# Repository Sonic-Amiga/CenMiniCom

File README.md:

# Schematics for the Centurion Minicomputer replica

This is my work in progress repository, documenting an attempt to build a replica of a
Centurion minicomputer. The repository is a fork of Meisaka's reverse engineering project
(https://github.com/Meisaka/CenMiniCom.git) and contains some modifications.

This is a rather complex project, consisting of a multiple boards. For more information about
boards, which have actually been worked on, please see a README.md file in corresponding board's
subdirectory.

#### IMPORTANT: Schematics are originally reverse engineered from multiple hi-res images of the various cards, so they may contain mistakes or errors.

# Contacts

Please direct all questions to pavel_fedin@mail.ru

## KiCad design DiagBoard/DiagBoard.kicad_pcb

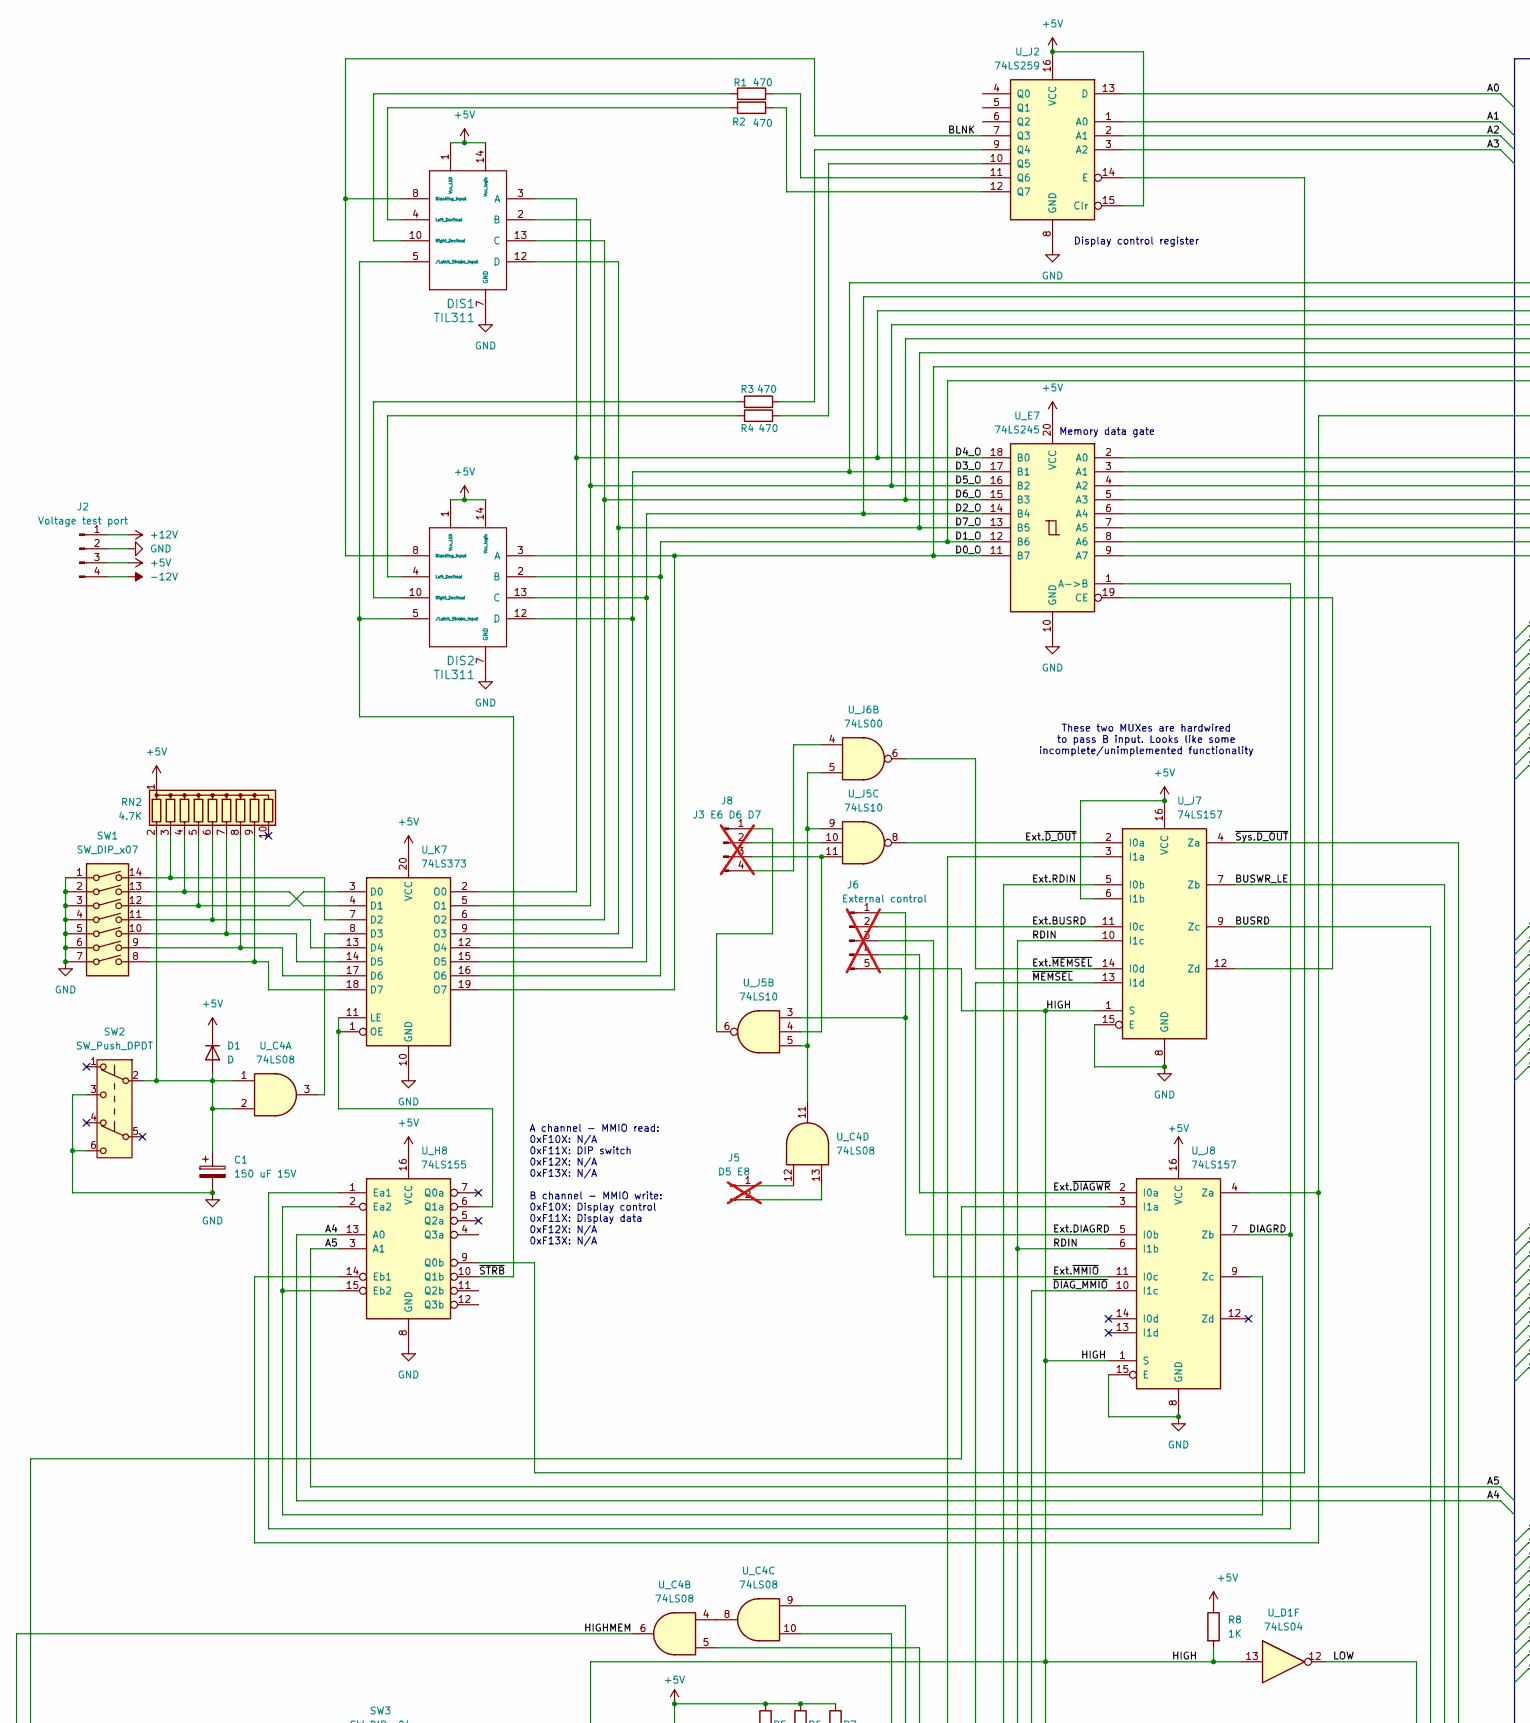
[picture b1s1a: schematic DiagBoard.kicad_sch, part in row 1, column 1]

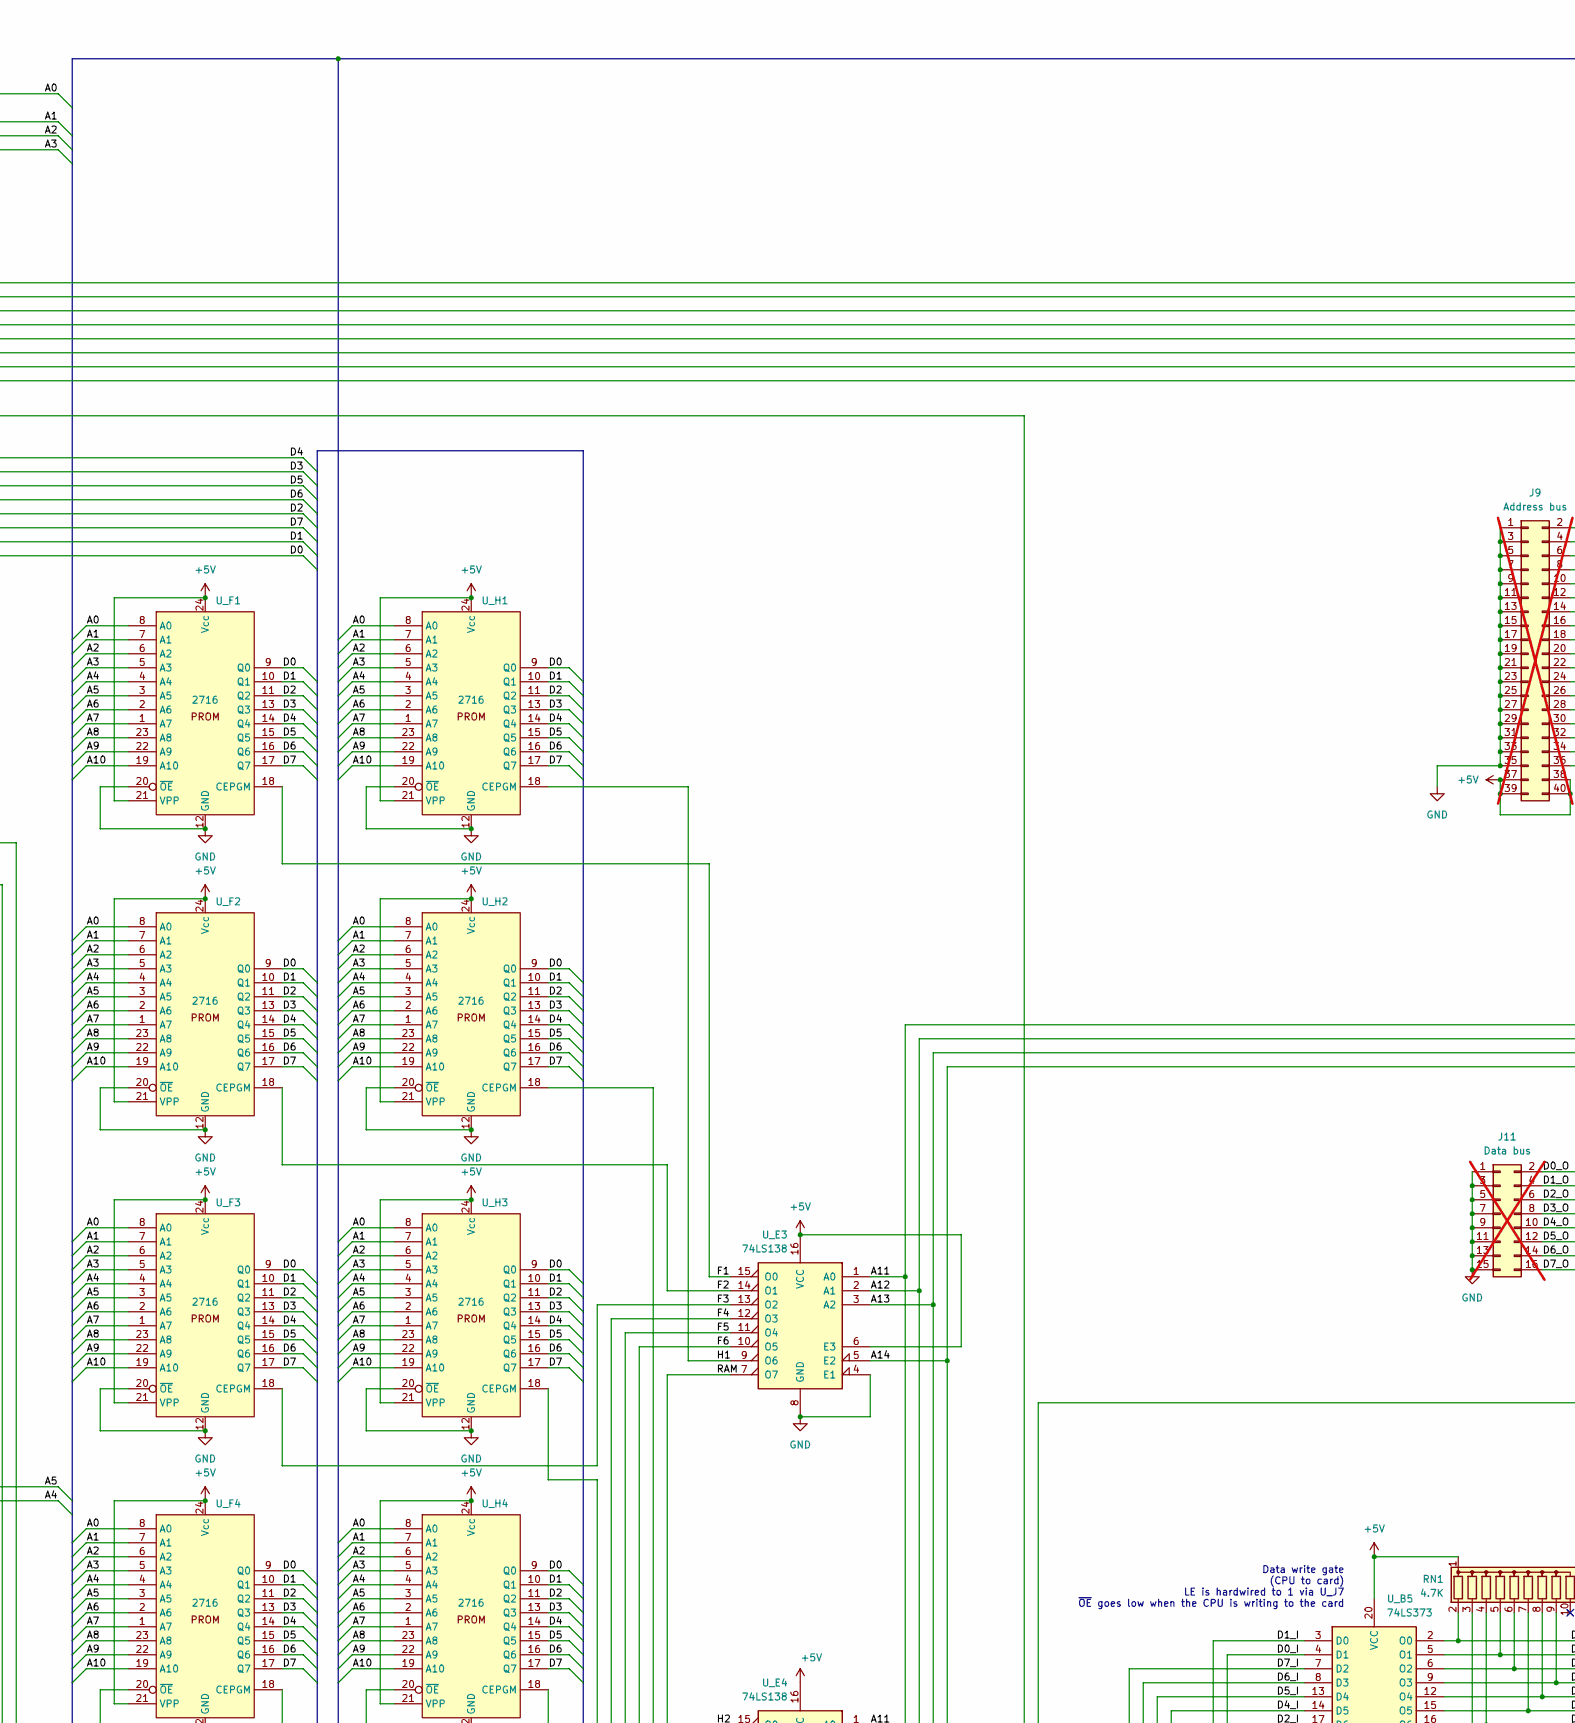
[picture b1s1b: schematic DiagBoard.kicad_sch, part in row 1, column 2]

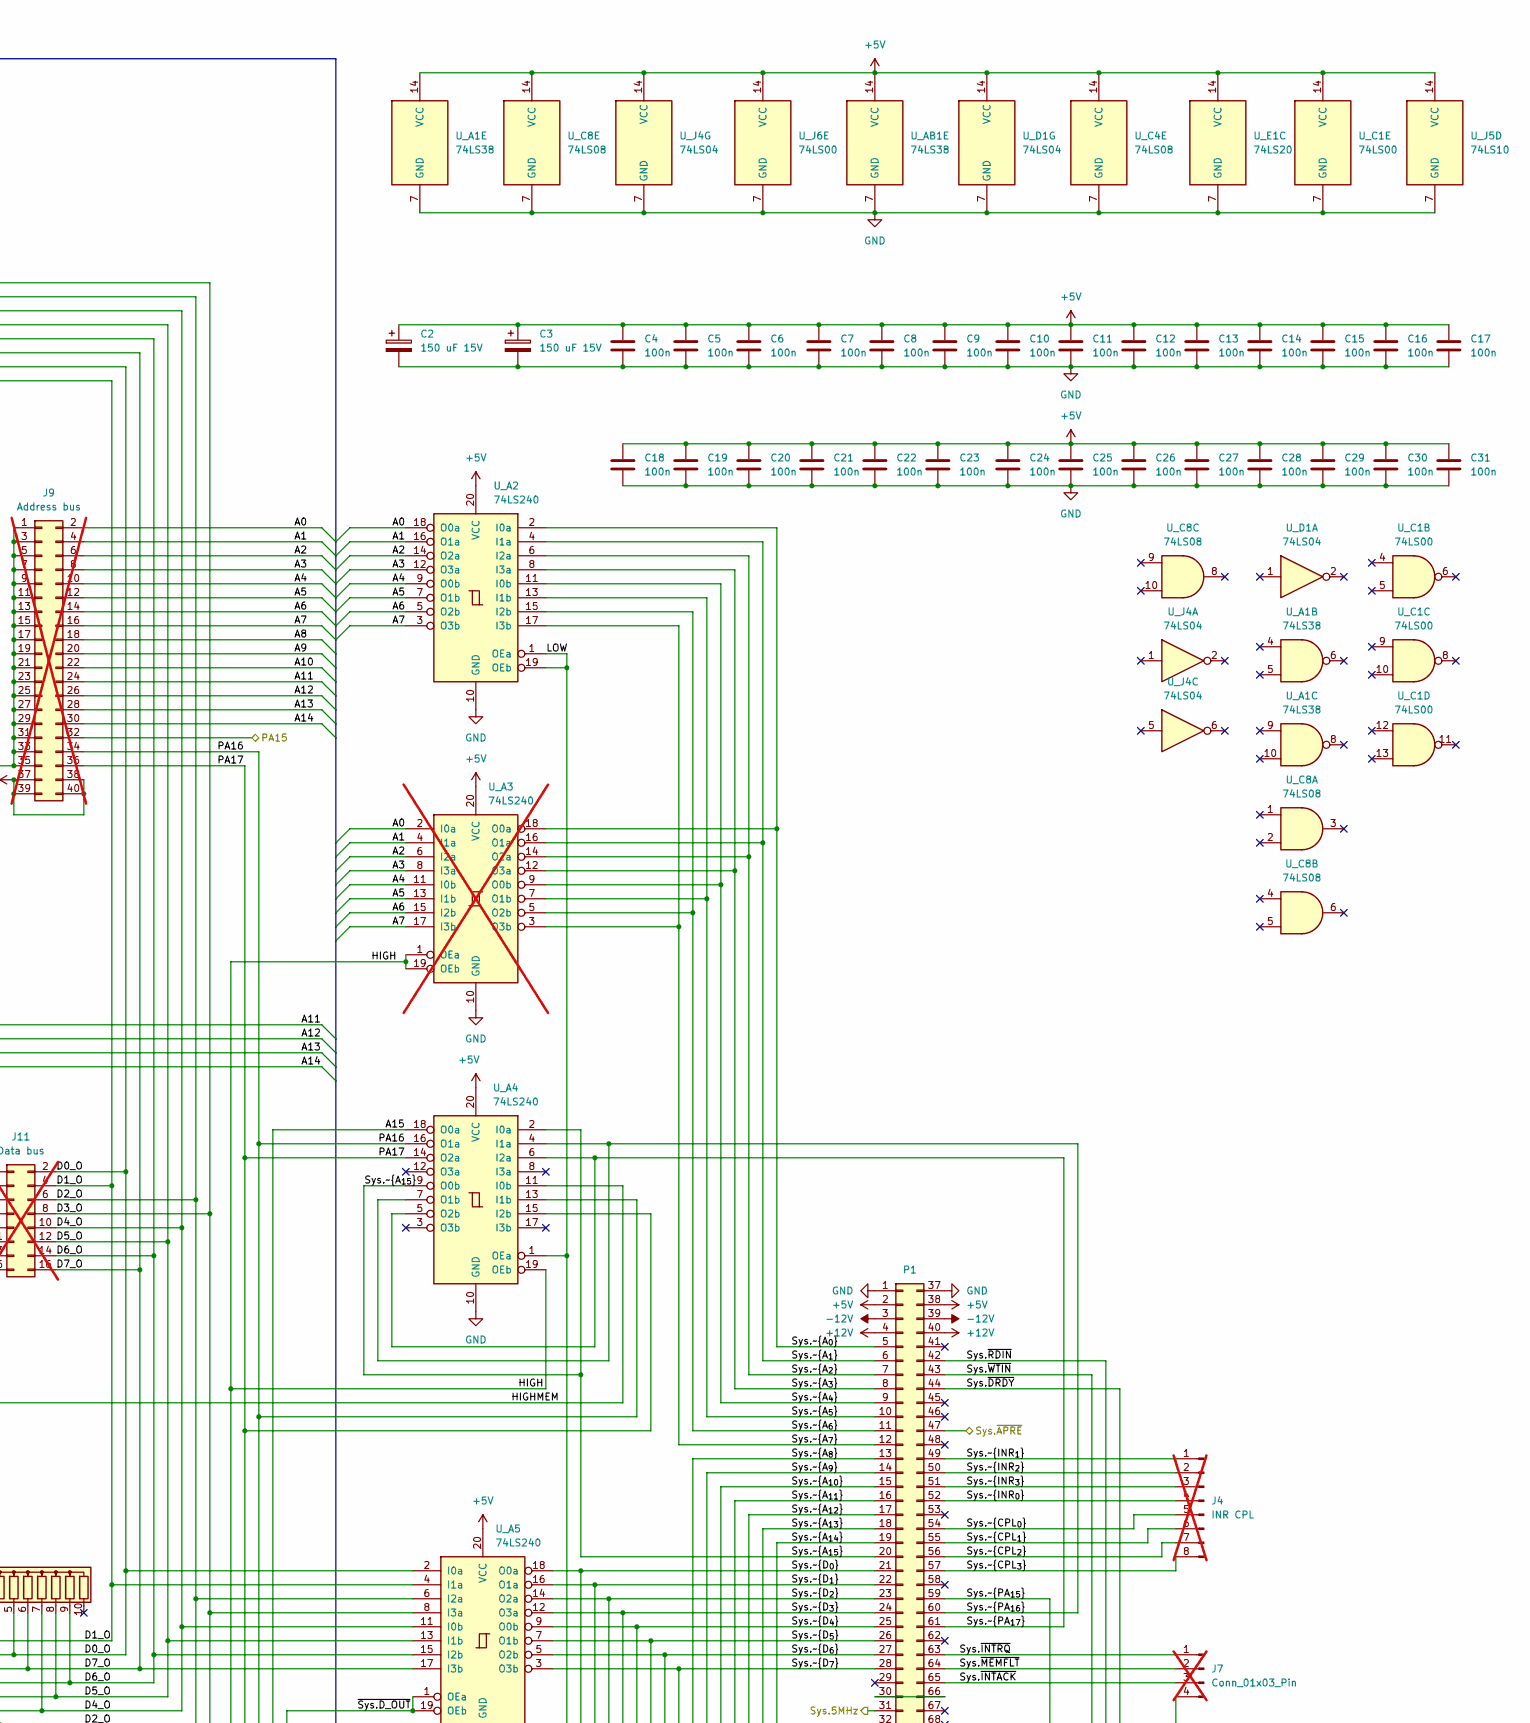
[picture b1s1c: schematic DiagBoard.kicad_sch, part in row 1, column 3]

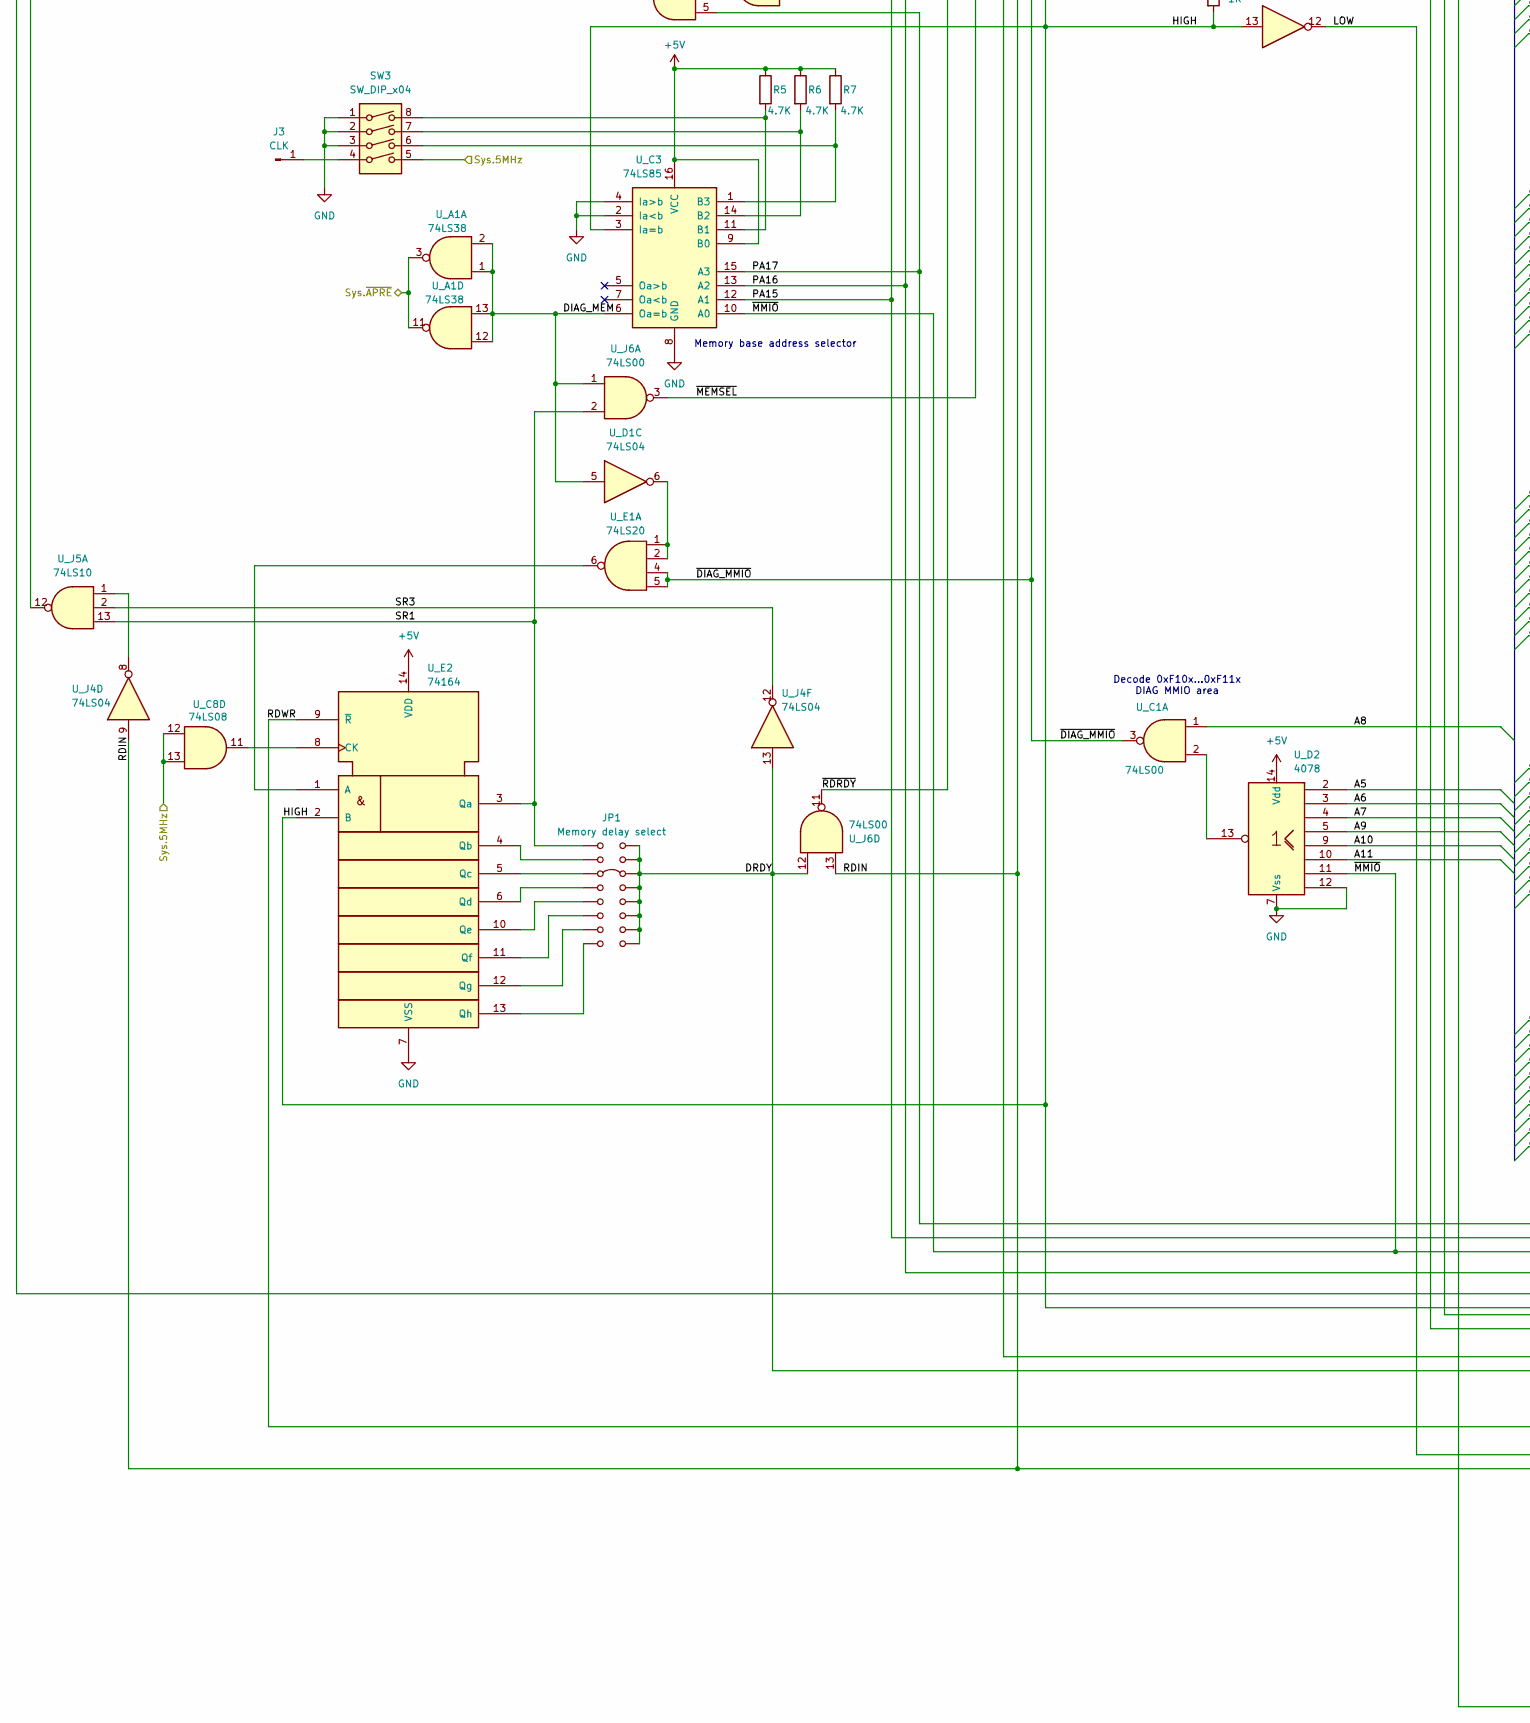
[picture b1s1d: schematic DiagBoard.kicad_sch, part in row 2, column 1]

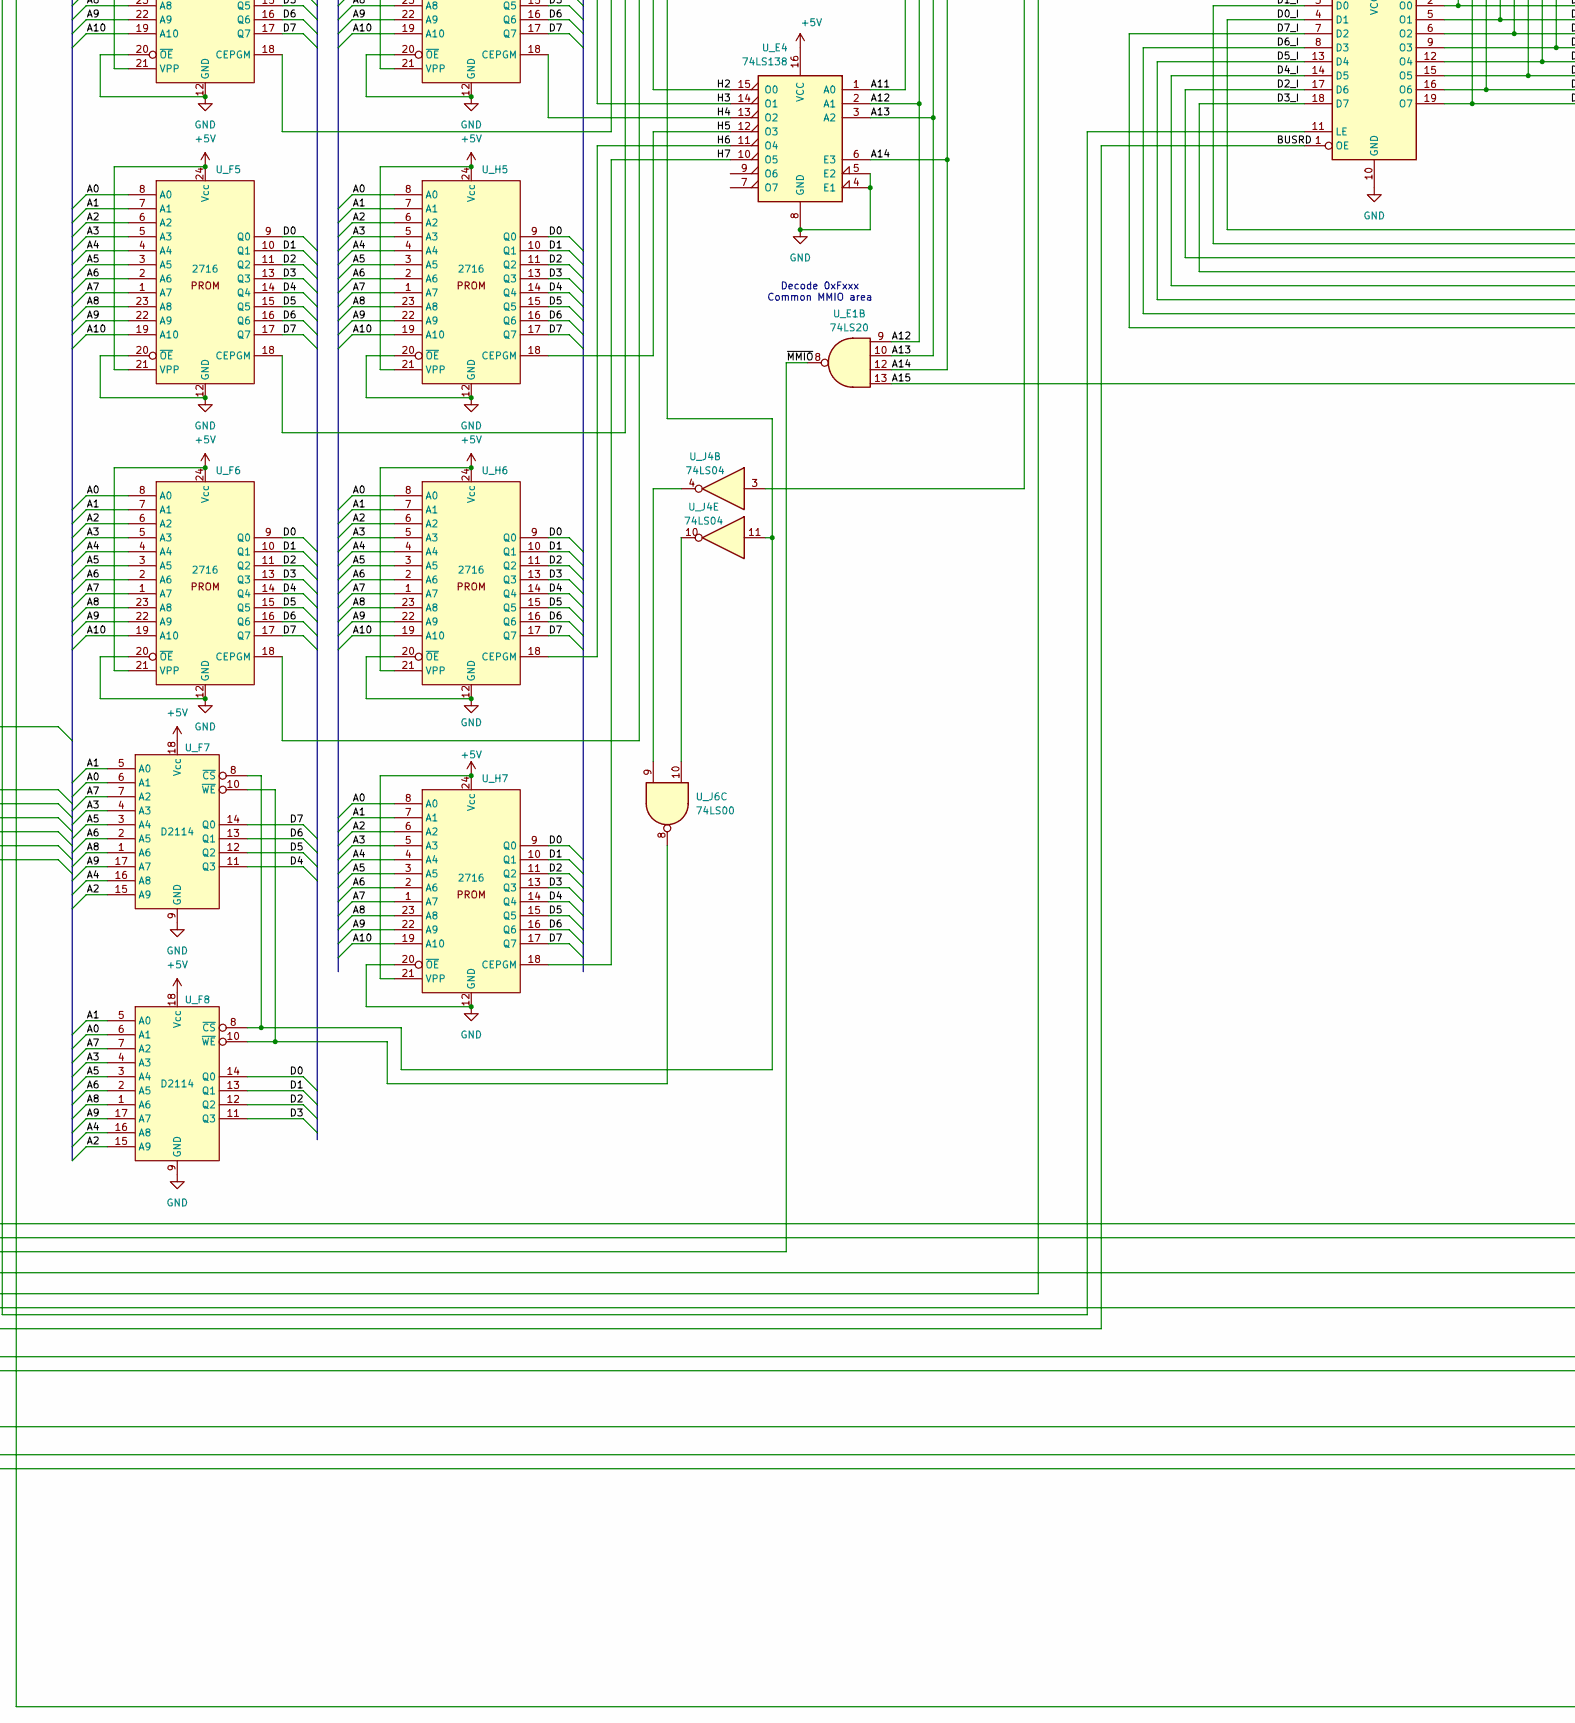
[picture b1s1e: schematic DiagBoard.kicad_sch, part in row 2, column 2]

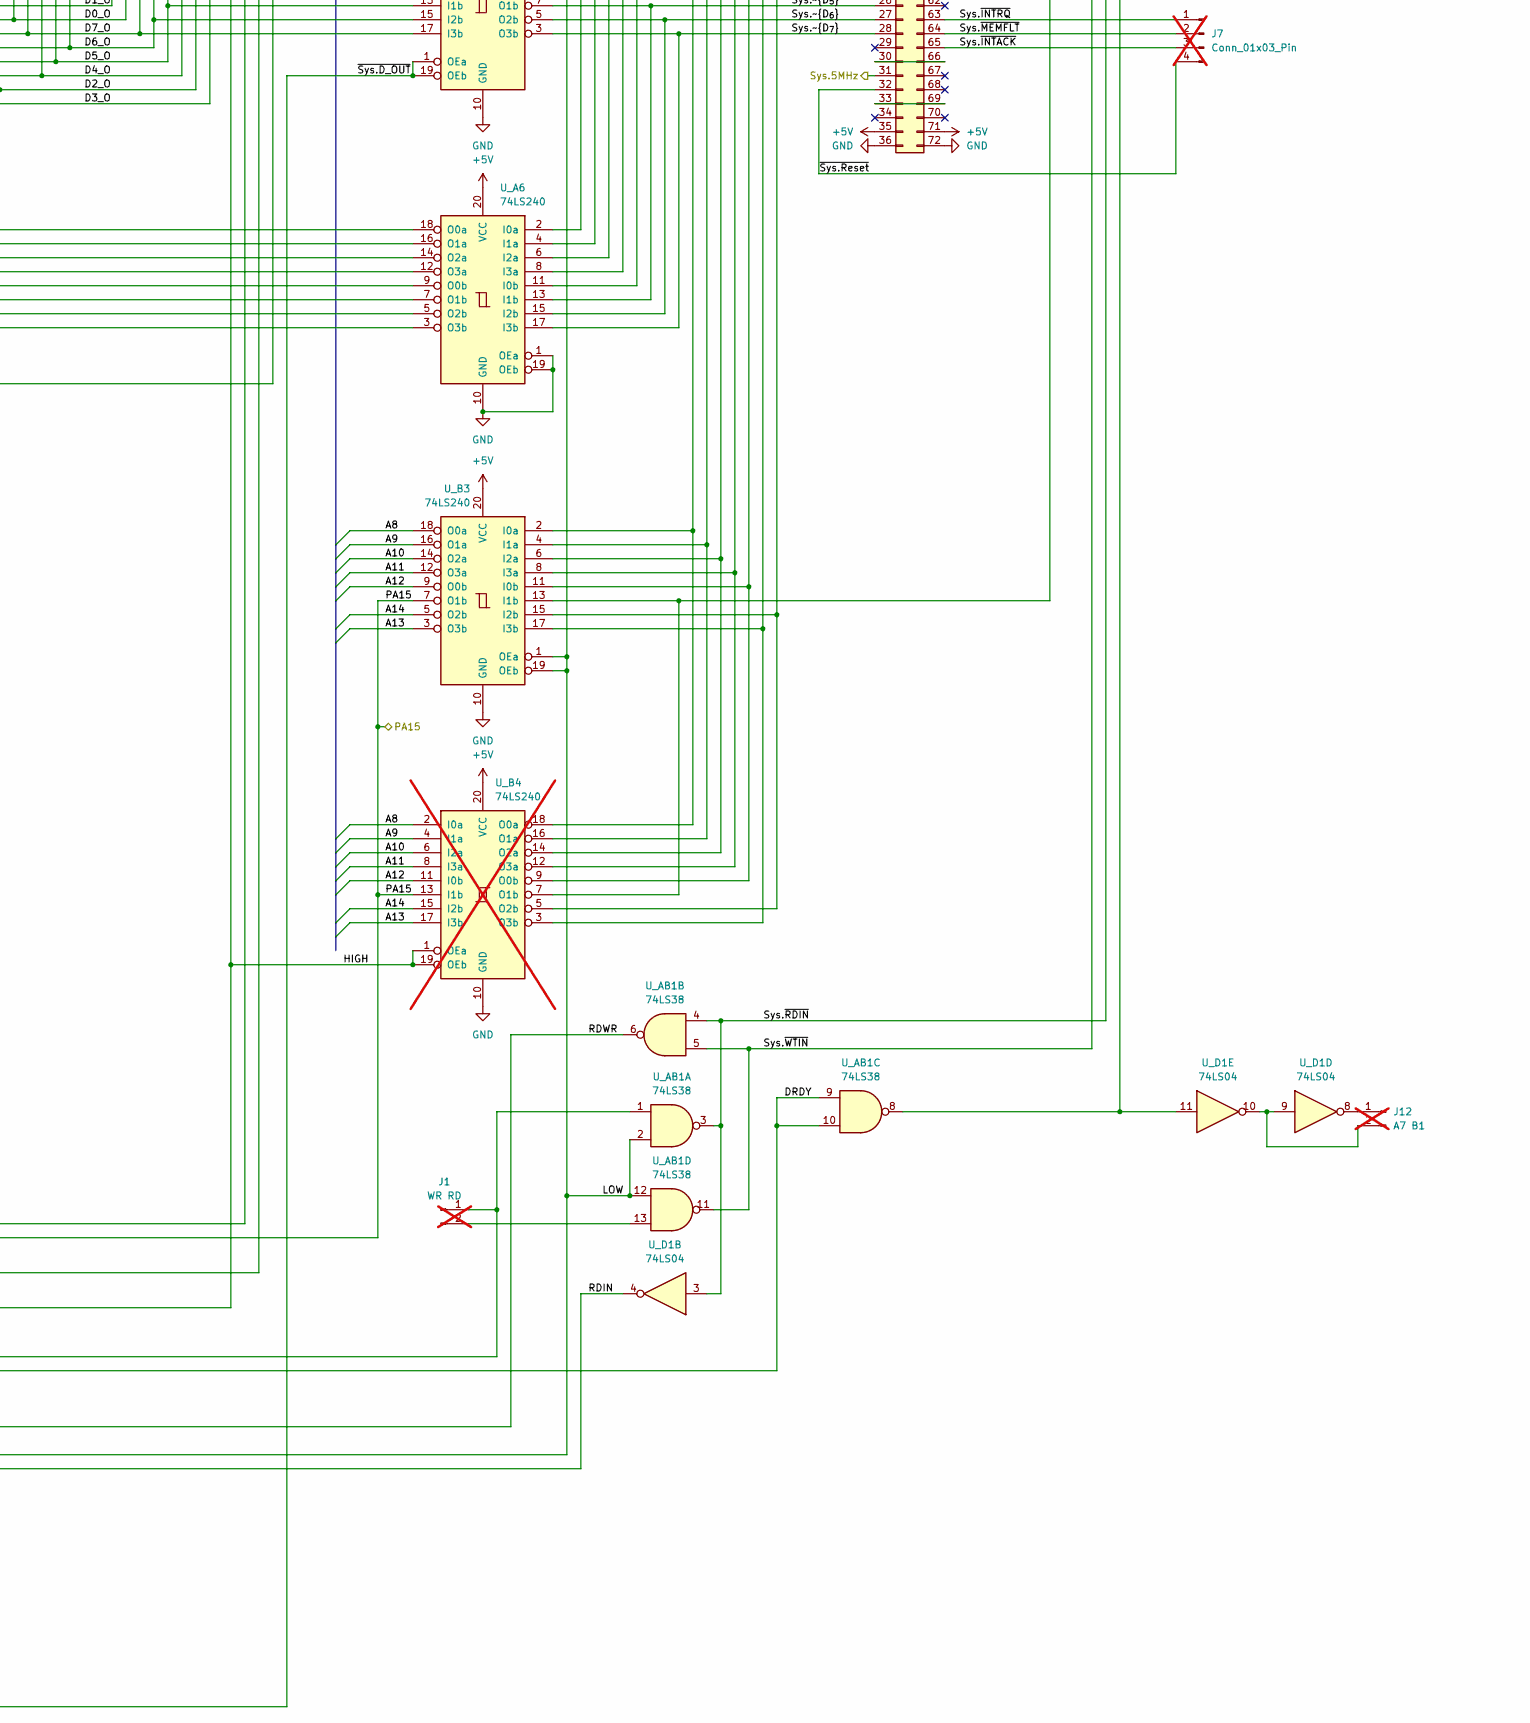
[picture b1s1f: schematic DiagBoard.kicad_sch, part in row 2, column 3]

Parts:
C1: 150 uF 15V; CP_Axial_L10.0mm_D4.5mm_P15.00mm_Horizontal
C2, C3: 150 uF 15V; CP_Axial_L25.0mm_D10.0mm_P30.00mm_Horizontal
C4, C5, C6, C7, C8, C9, C10, C11, C12, C13, C14, C15, C16, C17, C18, C19, C20, C21, C22, C23, C24, C25, C26, C27, C29, C30, C31: 100n; C_Disc_D4.3mm_W1.9mm_P5.00mm
C28: 100n; C_Rect_L9.0mm_W2.5mm_P7.50mm_MKT
D1: D; D_5W_P10.16mm_Horizontal
DIS1, DIS2: TIL311; DIP-14_W7.62mm_Socket
J1: WR RD; PinHeader_1x02_P2.54mm_Vertical; not fitted
J2: Voltage test port; Wago_734-134_1x04_P3.50mm_Vertical
J3: CLK; PinHeader_1x01_P2.54mm_Vertical
J4: INR CPL; PinHeader_1x08_P2.54mm_Vertical; not fitted
J5: D5 E8; PinHeader_1x02_P2.54mm_Vertical; not fitted
J6: External control; PinSocket_1x05_P2.54mm_Vertical; not fitted
J7: Conn_01x03_Pin; PinHeader_1x04_P2.54mm_Vertical; not fitted
J8: J3 E6 D6 D7; PinHeader_1x04_P2.54mm_Vertical; not fitted
J9: Address bus; IDC-Header_2x20_P2.54mm_Vertical; not fitted
J11: Data bus; IDC-Header_2x08_P2.54mm_Vertical; not fitted
J12: A7 B1; PinHeader_1x02_P2.54mm_Vertical; not fitted
JP1: Memory delay select; PinHeader_2x08_P2.54mm_Vertical
P1: Conn_02x36_Top_Bottom; BUS_EE200
R1, R2, R3, R4: 470; R_Axial_DIN0204_L3.6mm_D1.6mm_P7.62mm_Horizontal
R5, R6, R7: 4.7K; R_Axial_DIN0207_L6.3mm_D2.5mm_P10.16mm_Horizontal
R8: 1K; R_Axial_DIN0207_L6.3mm_D2.5mm_P10.16mm_Horizontal
RN1, RN2: 4.7K; R_Array_SIP10
SW1: SW_DIP_x07; SW_DIP_SPSTx07_Piano_10.8x19.34mm_W7.62mm_P2.54mm
SW2: SW_Push_DPDT; SW_Push_2P2T_Toggle_CK_PVA2OAH5xxxxxxV2
SW3: SW_DIP_x04; SW_DIP_SPSTx04_Slide_9.78x12.34mm_W7.62mm_P2.54mm
U_A1: 74LS38; DIP-14_W7.62mm
U_A2, U_A4, U_A5, U_A6: 74LS240; DIP-20_W7.62mm
U_A3: 74LS240; DIP-20_W7.62mm; not fitted
U_AB1: 74LS38; DIP-14_W7.62mm
U_B3: 74LS240; DIP-20_W7.62mm
U_B4: 74LS240; DIP-20_W7.62mm; not fitted
U_B5: 74LS373; DIP-20_W7.62mm
U_C1: 74LS00; DIP-14_W7.62mm
U_C3: 74LS85; DIP-16_W7.62mm
U_C4, U_C8: 74LS08; DIP-14_W7.62mm
U_D1: 74LS04; DIP-14_W7.62mm
U_D2: 4078; DIP-14_W7.62mm
U_E1: 74LS20; DIP-14_W7.62mm
U_E2: 74164; DIP-14_W7.62mm
U_E3, U_E4: 74LS138; DIP-16_W7.62mm
U_E7: 74LS245; DIP-20_W7.62mm
U_F1, U_F2, U_F3, U_F4, U_F5, U_F6: 2716; DIP-24_W15.24mm_Socket
U_F7, U_F8: D2114; DIP-18_W10.16mm
U_H1, U_H2, U_H3, U_H4, U_H5, U_H6, U_H7: 2716; DIP-24_W15.24mm_Socket
U_H8: 74LS155; DIP-16_W7.62mm
U_J2: 74LS259; DIP-16_W7.62mm
U_J4: 74LS04; DIP-14_W7.62mm
U_J5: 74LS10
U_J6: 74LS00; DIP-14_W7.62mm
U_J7, U_J8: 74LS157; DIP-16_W7.62mm
U_K7: 74LS373; DIP-20_W7.62mm

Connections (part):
+5V: C2.1, C3.1, C4.1, C5.1, C6.1, C7.1, C8.1, C9.1, C10.1, C11.1, C12.1, C13.1, C14.1, C15.1, C16.1, C17.1, C18.1, C19.1, C20.1, C21.1, C22.1, C23.1, C24.1, C25.1, C26.1, C27.1, C28.1, C29.1, C30.1, C31.1, D1.1 (K), DIS1.1 (Vcc_LED), DIS1.14 (Vcc_logic), DIS2.1 (Vcc_LED), DIS2.14 (Vcc_logic), J2.3, J9.37, J9.38, J9.39, J9.40, P1.2, P1.35, P1.38, P1.71, R5.1, R6.1, R7.1, R8.1, RN1.1 (common), RN2.1 (common), U_A1.14 (VCC), U_A2.20 (VCC), U_A3.20 (VCC), U_A4.20 (VCC), U_A5.20 (VCC), U_A6.20 (VCC), U_AB1.14 (VCC), U_B3.20 (VCC), U_B4.20 (VCC), U_B5.20 (VCC), U_C1.14 (VCC), U_C3.9 (B0), U_C3.16 (VCC), U_C4.14 (VCC), U_C8.14 (VCC), U_D1.14 (VCC), U_D2.14 (Vdd), U_E1.14 (VCC), U_E2.14 (VDD), U_E3.6 (E3), U_E3.16 (VCC), U_E4.16 (VCC), U_E7.20 (VCC), U_F1.21 (VPP), U_F1.24 (Vcc), U_F2.21 (VPP), U_F2.24 (Vcc), U_F3.21 (VPP), U_F3.24 (Vcc), U_F4.21 (VPP), U_F4.24 (Vcc), U_F5.21 (VPP), U_F5.24 (Vcc), U_F6.21 (VPP), U_F6.24 (Vcc)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
+12V: J2.1, P1.4, P1.40
-12V: J2.4, P1.3, P1.39
/A0: J9.2, U_A2.18 (O0a), U_A3.2 (I0a), U_F1.8 (A0), U_F2.8 (A0), U_F3.8 (A0), U_F4.8 (A0), U_F5.8 (A0), U_F6.8 (A0), U_F7.6 (A1), U_F8.6 (A1), U_H1.8 (A0), U_H2.8 (A0), U_H3.8 (A0), U_H4.8 (A0), U_H5.8 (A0), U_H6.8 (A0), U_H7.8 (A0), U_J2.13 (D)
/A1: J9.4, U_A2.16 (O1a), U_A3.4 (I1a), U_F1.7 (A1), U_F2.7 (A1), U_F3.7 (A1), U_F4.7 (A1), U_F5.7 (A1), U_F6.7 (A1), U_F7.5 (A0), U_F8.5 (A0), U_H1.7 (A1), U_H2.7 (A1), U_H3.7 (A1), U_H4.7 (A1), U_H5.7 (A1), U_H6.7 (A1), U_H7.7 (A1), U_J2.1 (A0)
/A2: J9.6, U_A2.14 (O2a), U_A3.6 (I2a), U_F1.6 (A2), U_F2.6 (A2), U_F3.6 (A2), U_F4.6 (A2), U_F5.6 (A2), U_F6.6 (A2), U_F7.15 (A9), U_F8.15 (A9), U_H1.6 (A2), U_H2.6 (A2), U_H3.6 (A2), U_H4.6 (A2), U_H5.6 (A2), U_H6.6 (A2), U_H7.6 (A2), U_J2.2 (A1)
/A3: J9.8, U_A2.12 (O3a), U_A3.8 (I3a), U_F1.5 (A3), U_F2.5 (A3), U_F3.5 (A3), U_F4.5 (A3), U_F5.5 (A3), U_F6.5 (A3), U_F7.4 (A3), U_F8.4 (A3), U_H1.5 (A3), U_H2.5 (A3), U_H3.5 (A3), U_H4.5 (A3), U_H5.5 (A3), U_H6.5 (A3), U_H7.5 (A3), U_J2.3 (A2)
/A4: J9.10, U_A2.9 (O0b), U_A3.11 (I0b), U_F1.4 (A4), U_F2.4 (A4), U_F3.4 (A4), U_F4.4 (A4), U_F5.4 (A4), U_F6.4 (A4), U_F7.16 (A8), U_F8.16 (A8), U_H1.4 (A4), U_H2.4 (A4), U_H3.4 (A4), U_H4.4 (A4), U_H5.4 (A4), U_H6.4 (A4), U_H7.4 (A4), U_H8.13 (A0)
/A5: J9.12, U_A2.7 (O1b), U_A3.13 (I1b), U_D2.2, U_F1.3 (A5), U_F2.3 (A5), U_F3.3 (A5), U_F4.3 (A5), U_F5.3 (A5), U_F6.3 (A5), U_F7.3 (A4), U_F8.3 (A4), U_H1.3 (A5), U_H2.3 (A5), U_H3.3 (A5), U_H4.3 (A5), U_H5.3 (A5), U_H6.3 (A5), U_H7.3 (A5), U_H8.3 (A1)
/A6: J9.14, U_A2.5 (O2b), U_A3.15 (I2b), U_D2.3, U_F1.2 (A6), U_F2.2 (A6), U_F3.2 (A6), U_F4.2 (A6), U_F5.2 (A6), U_F6.2 (A6), U_F7.2 (A5), U_F8.2 (A5), U_H1.2 (A6), U_H2.2 (A6), U_H3.2 (A6), U_H4.2 (A6), U_H5.2 (A6), U_H6.2 (A6), U_H7.2 (A6)
/A7: J9.16, U_A2.3 (O3b), U_A3.17 (I3b), U_D2.4, U_F1.1 (A7), U_F2.1 (A7), U_F3.1 (A7), U_F4.1 (A7), U_F5.1 (A7), U_F6.1 (A7), U_F7.7 (A2), U_F8.7 (A2), U_H1.1 (A7), U_H2.1 (A7), U_H3.1 (A7), U_H4.1 (A7), U_H5.1 (A7), U_H6.1 (A7), U_H7.1 (A7)
/A8: J9.18, U_B3.18 (O0a), U_B4.2 (I0a), U_C1.1, U_F1.23 (A8), U_F2.23 (A8), U_F3.23 (A8), U_F4.23 (A8), U_F5.23 (A8), U_F6.23 (A8), U_F7.1 (A6), U_F8.1 (A6), U_H1.23 (A8), U_H2.23 (A8), U_H3.23 (A8), U_H4.23 (A8), U_H5.23 (A8), U_H6.23 (A8), U_H7.23 (A8)
/A9: J9.20, U_B3.16 (O1a), U_B4.4 (I1a), U_D2.5, U_F1.22 (A9), U_F2.22 (A9), U_F3.22 (A9), U_F4.22 (A9), U_F5.22 (A9), U_F6.22 (A9), U_F7.17 (A7), U_F8.17 (A7), U_H1.22 (A9), U_H2.22 (A9), U_H3.22 (A9), U_H4.22 (A9), U_H5.22 (A9), U_H6.22 (A9), U_H7.22 (A9)
/A10: J9.22, U_B3.14 (O2a), U_B4.6 (I2a), U_D2.9, U_F1.19 (A10), U_F2.19 (A10), U_F3.19 (A10), U_F4.19 (A10), U_F5.19 (A10), U_F6.19 (A10), U_H1.19 (A10), U_H2.19 (A10), U_H3.19 (A10), U_H4.19 (A10), U_H5.19 (A10), U_H6.19 (A10), U_H7.19 (A10)
/A11: J9.24, U_B3.12 (O3a), U_B4.8 (I3a), U_D2.10, U_E3.1 (A0), U_E4.1 (A0)
/A12: J9.26, U_B3.9 (O0b), U_B4.11 (I0b), U_E1.9, U_E3.2 (A1), U_E4.2 (A1)
/A13: J9.28, U_B3.3 (O3b), U_B4.17 (I3b), U_E1.10, U_E3.3 (A2), U_E4.3 (A2)
/A14: J9.30, U_B3.5 (O2b), U_B4.15 (I2b), U_E1.12, U_E3.5 (E2), U_E4.6 (E3)
/A15: U_A4.18 (O0a), U_E1.13
/BLNK: DIS1.8 (Blanking_Input), DIS2.8 (Blanking_Input), U_J2.7 (Q3)
/BUSRD: U_B5.1 (OE), U_J7.9 (Zc)
/BUSWR_LE: U_B5.11 (LE), U_J7.7 (Zb)
/D0: U_E7.9 (A7), U_F1.9 (Q0), U_F2.9 (Q0), U_F3.9 (Q0), U_F4.9 (Q0), U_F5.9 (Q0), U_F6.9 (Q0), U_F8.14 (Q0), U_H1.9 (Q0), U_H2.9 (Q0), U_H3.9 (Q0), U_H4.9 (Q0), U_H5.9 (Q0), U_H6.9 (Q0), U_H7.9 (Q0)
/D0_I: U_A6.18 (O0a), U_B5.4 (D1)
/D0_O: DIS2.3 (A), J11.2, RN1.5 (R4), U_A5.2 (I0a), U_B5.5 (O1), U_E7.11 (B7), U_K7.19 (O7)
/D1: U_E7.8 (A6), U_F1.10 (Q1), U_F2.10 (Q1), U_F3.10 (Q1), U_F4.10 (Q1), U_F5.10 (Q1), U_F6.10 (Q1), U_F8.13 (Q1), U_H1.10 (Q1), U_H2.10 (Q1), U_H3.10 (Q1), U_H4.10 (Q1), U_H5.10 (Q1), U_H6.10 (Q1), U_H7.10 (Q1)
/D1_I: U_A6.16 (O1a), U_B5.3 (D0)
/D1_O: DIS2.2 (B), J11.4, RN1.2 (R1), U_A5.4 (I1a), U_B5.2 (O0), U_E7.12 (B6), U_K7.16 (O6)
/D2: U_E7.6 (A4), U_F1.11 (Q2), U_F2.11 (Q2), U_F3.11 (Q2), U_F4.11 (Q2), U_F5.11 (Q2), U_F6.11 (Q2), U_F8.12 (Q2), U_H1.11 (Q2), U_H2.11 (Q2), U_H3.11 (Q2), U_H4.11 (Q2), U_H5.11 (Q2), U_H6.11 (Q2), U_H7.11 (Q2)
/D2_I: U_A6.14 (O2a), U_B5.17 (D6)
/D2_O: DIS2.13 (C), J11.6, RN1.4 (R3), U_A5.6 (I2a), U_B5.16 (O6), U_E7.14 (B4), U_K7.15 (O5)
/D3: U_E7.3 (A1), U_F1.13 (Q3), U_F2.13 (Q3), U_F3.13 (Q3), U_F4.13 (Q3), U_F5.13 (Q3), U_F6.13 (Q3), U_F8.11 (Q3), U_H1.13 (Q3), U_H2.13 (Q3), U_H3.13 (Q3), U_H4.13 (Q3), U_H5.13 (Q3), U_H6.13 (Q3), U_H7.13 (Q3)
/D3_I: U_A6.12 (O3a), U_B5.18 (D7)
/D3_O: DIS2.12 (D), J11.8, RN1.3 (R2), U_A5.8 (I3a), U_B5.19 (O7), U_E7.17 (B1), U_K7.12 (O4)
/D4: U_E7.2 (A0), U_F1.14 (Q4), U_F2.14 (Q4), U_F3.14 (Q4), U_F4.14 (Q4), U_F5.14 (Q4), U_F6.14 (Q4), U_F7.11 (Q3), U_H1.14 (Q4), U_H2.14 (Q4), U_H3.14 (Q4), U_H4.14 (Q4), U_H5.14 (Q4), U_H6.14 (Q4), U_H7.14 (Q4)
/D4_I: U_A6.9 (O0b), U_B5.14 (D5)
/D4_O: DIS1.3 (A), J11.10, RN1.7 (R6), U_A5.11 (I0b), U_B5.15 (O5), U_E7.18 (B0), U_K7.2 (O0)
/D5: U_E7.4 (A2), U_F1.15 (Q5), U_F2.15 (Q5), U_F3.15 (Q5), U_F4.15 (Q5), U_F5.15 (Q5), U_F6.15 (Q5), U_F7.12 (Q2), U_H1.15 (Q5), U_H2.15 (Q5), U_H3.15 (Q5), U_H4.15 (Q5), U_H5.15 (Q5), U_H6.15 (Q5), U_H7.15 (Q5)
/D5_I: U_A6.7 (O1b), U_B5.13 (D4)
/D5_O: DIS1.2 (B), J11.12, RN1.8 (R7), U_A5.13 (I1b), U_B5.12 (O4), U_E7.16 (B2), U_K7.5 (O1)
/D6: U_E7.5 (A3), U_F1.16 (Q6), U_F2.16 (Q6), U_F3.16 (Q6), U_F4.16 (Q6), U_F5.16 (Q6), U_F6.16 (Q6), U_F7.13 (Q1), U_H1.16 (Q6), U_H2.16 (Q6), U_H3.16 (Q6), U_H4.16 (Q6), U_H5.16 (Q6), U_H6.16 (Q6), U_H7.16 (Q6)
/D6_I: U_A6.5 (O2b), U_B5.8 (D3)
/D6_O: DIS1.13 (C), J11.14, RN1.9 (R8), U_A5.15 (I2b), U_B5.9 (O3), U_E7.15 (B3), U_K7.6 (O2)
/D7: U_E7.7 (A5), U_F1.17 (Q7), U_F2.17 (Q7), U_F3.17 (Q7), U_F4.17 (Q7), U_F5.17 (Q7), U_F6.17 (Q7), U_F7.14 (Q0), U_H1.17 (Q7), U_H2.17 (Q7), U_H3.17 (Q7), U_H4.17 (Q7), U_H5.17 (Q7), U_H6.17 (Q7), U_H7.17 (Q7)
/D7_I: U_A6.3 (O3b), U_B5.7 (D2)
/D7_O: DIS1.12 (D), J11.16, RN1.6 (R5), U_A5.17 (I3b), U_B5.6 (O2), U_E7.13 (B5), U_K7.9 (O3)
/DIAGRD: U_E7.1 (A->B), U_H8.1 (Ea1), U_J8.7 (Zb)
/DIAG_MEM: U_A1.1, U_A1.2, U_A1.12, U_A1.13, U_C3.6 (Oa=b), U_D1.5, U_J6.1
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
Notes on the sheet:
Memory data gate
Decode 0xFxxx Common MMIO area
Memory base address selector
Data write gate (CPU to card) LE is hardwired to 1 via U_J7 ~{OE} goes low when the CPU is writing to the card
A channel - MMIO read: 0xF10X: N/A 0xF11X: DIP switch 0xF12X: N/A 0xF13X: N/A B channel - MMIO write: 0xF10X: Display control 0xF11X: Display data 0xF12X: N/A 0xF13X: N/A
These two MUXes are hardwired to pass B input. Looks like some incomplete/unimplemented functionality
Decode 0xF10x...0xF11x DIAG MMIO area
Display control register

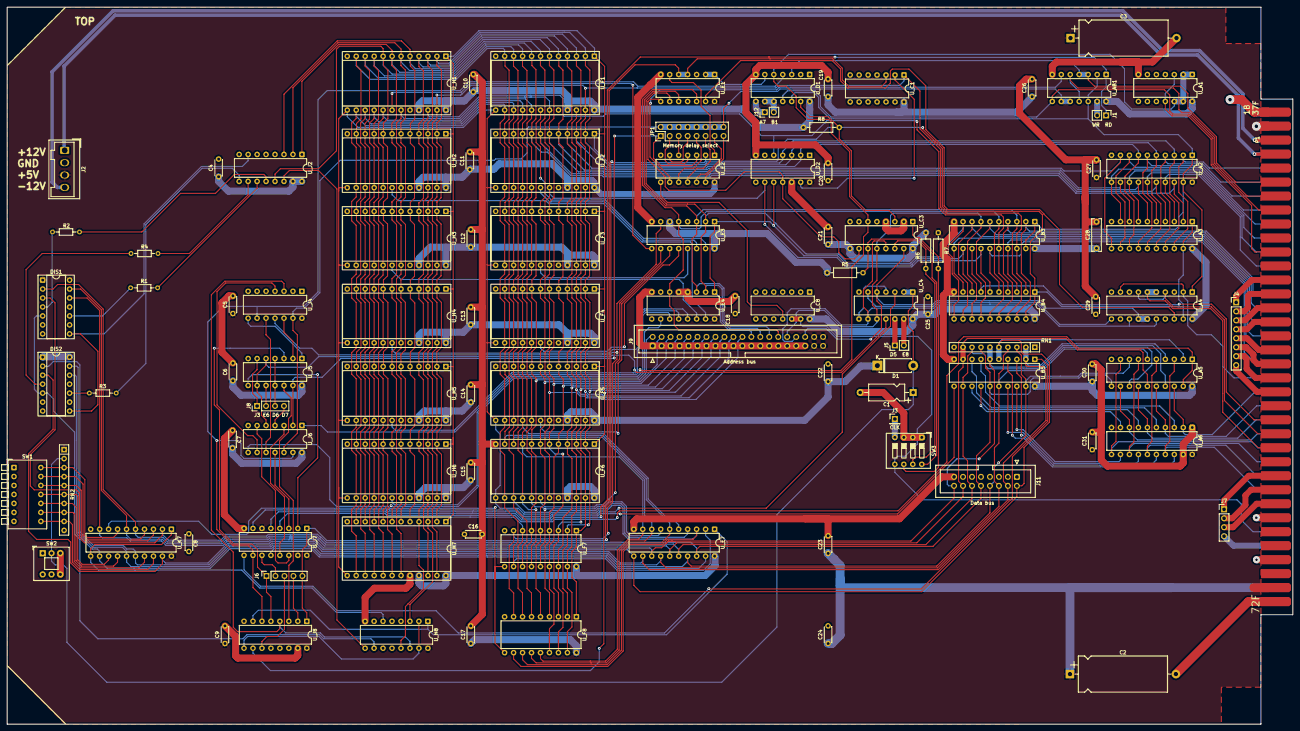
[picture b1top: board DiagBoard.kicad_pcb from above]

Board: 4 copper layers, 364.0 x 203.0 mm, 104 parts (0 on the bottom side), 186 nets.
